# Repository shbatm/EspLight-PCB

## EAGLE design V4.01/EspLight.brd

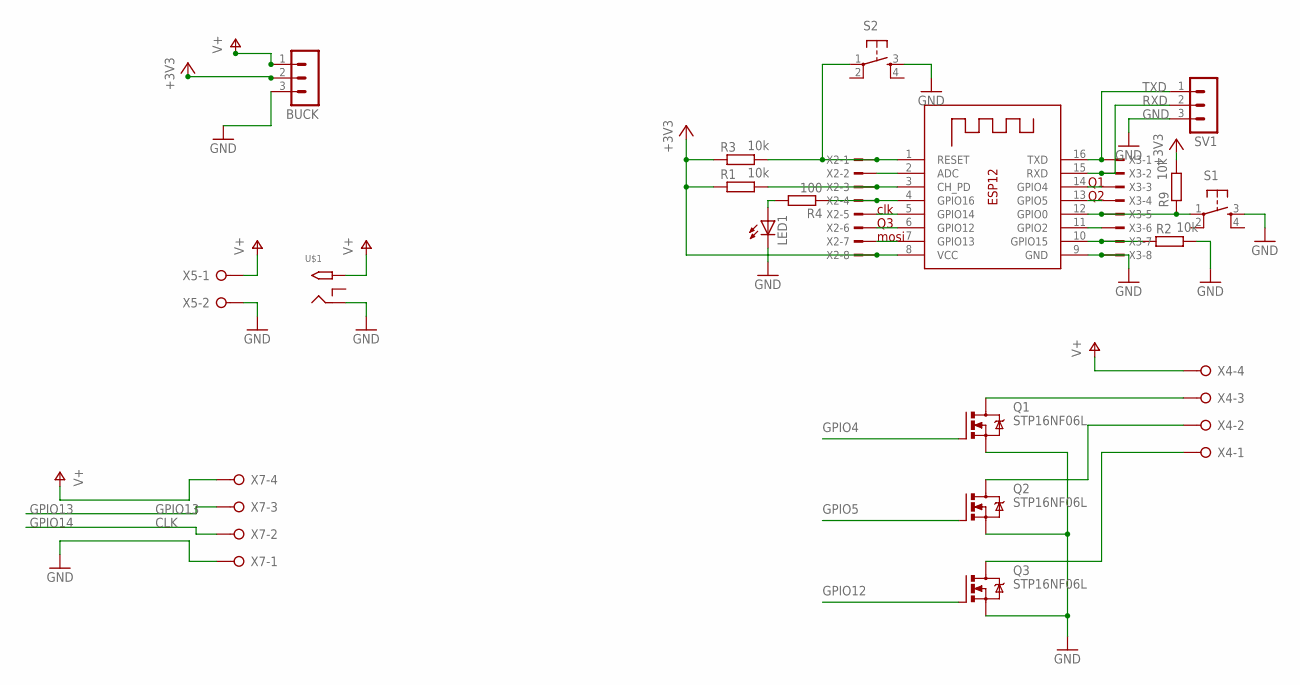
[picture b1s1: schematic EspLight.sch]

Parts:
BUCK: MA03-1
LED1: LED5MM
Q1, Q2, Q3: STP16NF06L; TO220BV
R1, R2, R3, R9: 10k; 0207/10
R4: 100; 0207/10
S1, S2: TAC_SWITCHPTH; TACTILE-PTH
SV1: MA03-1
U$1: 2.1MMJACKTHM; PJ-102A
X1: ESP-12
X2, X3: TSW-108-02-S-S
X4, X7: W237-04P; W237-4P
X5: W237-02P; W237-132

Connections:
+3V3: BUCK.2, R1.1, R3.1, R9.2, X1.8 (VCC), X2.8
GND: BUCK.3, LED1.K (C), Q1.S, Q2.S, Q3.S, R2.2, S1.3, S2.3, SV1.3, U$1.RING, X1.9 (GND), X3.8, X5.2, X7.1
GPIO2: X1.11 (GPIO2), X3.6
GPIO4: Q1.G, X1.14 (GPIO4), X3.3
GPIO5: Q2.G, X1.13 (GPIO5), X3.4
GPIO12: Q3.G, X1.6 (GPIO12), X2.6
GPIO13: X1.7 (GPIO13), X2.7, X7.3
GPIO14: X1.5 (GPIO14), X2.5, X7.2
unnamed: R3.2, S2.1, X1.1 (RESET), X2.1
unnamed: R1.2, X1.3 (CH_PD), X2.3
unnamed: R2.1, X1.10 (GPIO15), X3.7
unnamed: R4.1, X1.4 (GPIO16), X2.4
unnamed: R9.1, S1.1, X1.12 (GPIO0), X3.5
unnamed: X1.2 (ADC), X2.2
unnamed: LED1.A, R4.2
unnamed: Q1.D, X4.3
unnamed: Q2.D, X4.2
unnamed: Q3.D, X4.1
RXD: SV1.2, X1.15 (RXD), X3.2
TXD: SV1.1, X1.16 (TXD), X3.1
V+: BUCK.1, U$1.TIP, X4.4, X5.1, X7.4

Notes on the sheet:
clk
mosi
CLK

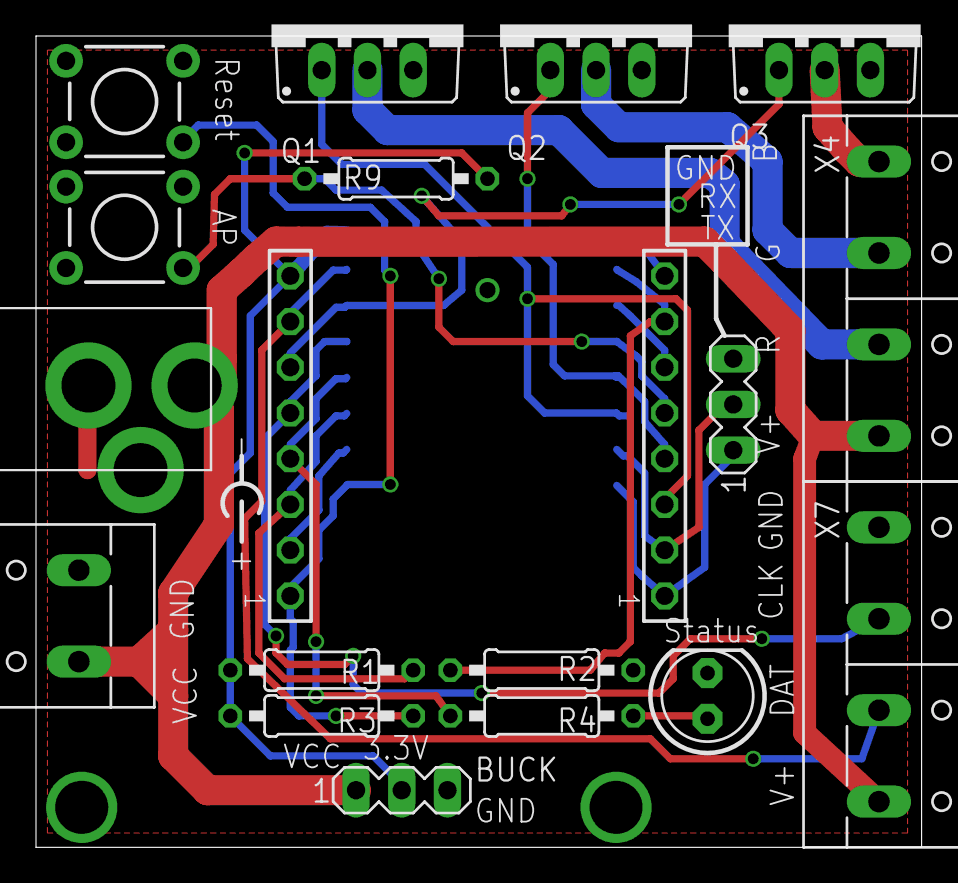
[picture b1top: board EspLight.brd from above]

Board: 2 copper layers, 49.2 x 45.1 mm, 20 parts (1 on the bottom side), 21 nets.

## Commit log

2016-09-22 V4.01 - Off-board Buck and Mounting Change
    New version of board with off-board Buck Converter and a change in the mounting pattern to shrink the board size slightly.
2016-09-22 Add Google Sketchup Files
2016-09-22 V4.03 - Uploaded correct board
2016-09-22 eagleUp - EAGLE to Sketchup Files

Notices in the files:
parts and their libraries:
SparkFun-Retired: Licensing:Creative Commons ShareAlike 4.0 International - https://creativecommons.org/licenses/by-sa/4.0
